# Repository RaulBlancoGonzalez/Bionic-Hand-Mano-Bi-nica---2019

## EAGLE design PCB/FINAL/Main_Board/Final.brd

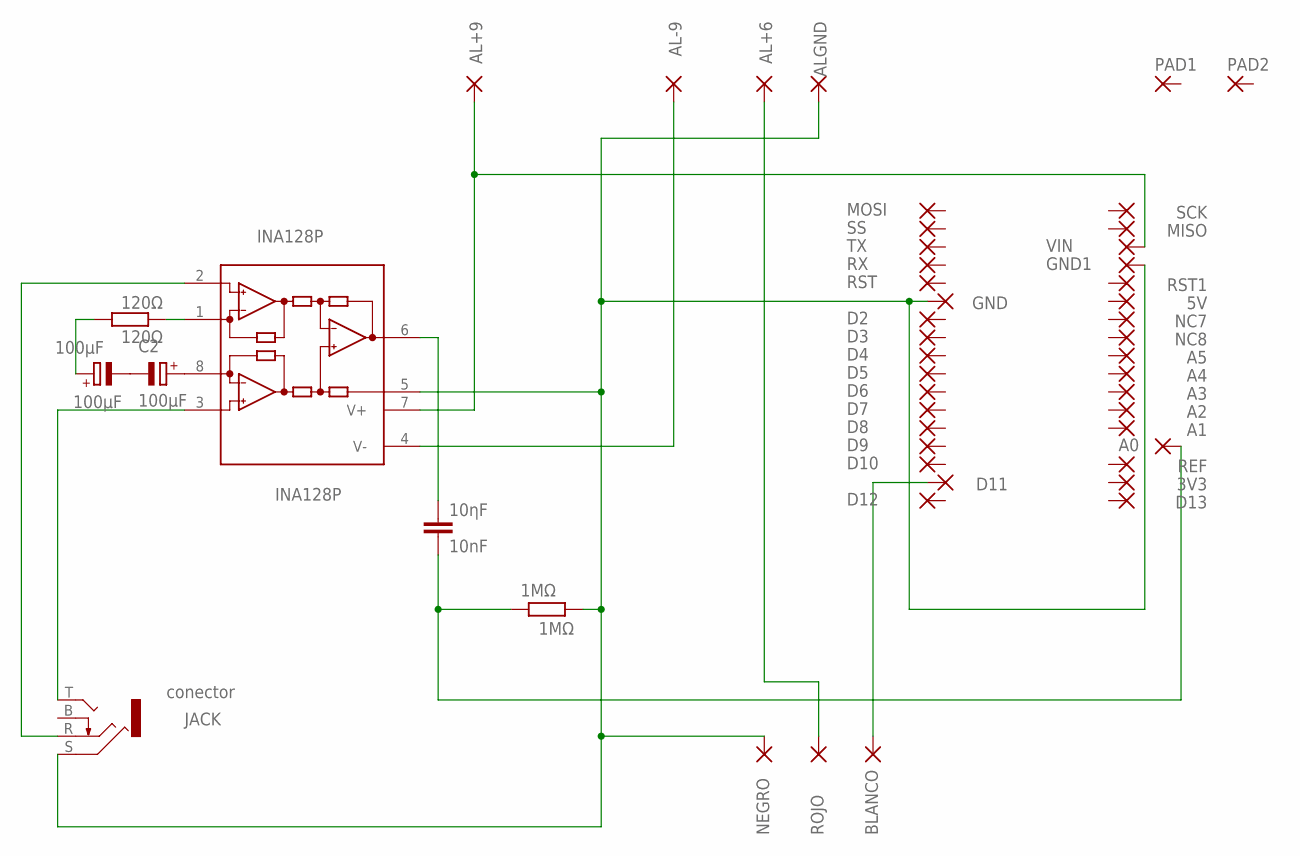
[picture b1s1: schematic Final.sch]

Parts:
1MΩ: 1MΩ; 0207/15
3V3, 5V: 1,6/0,9
10ηF: 10nF; C050-030X075
100μF: 100μF; B45181B
120Ω: 120Ω; 0207/15
A0, A1, A2, A3, A4, A5: 1,6/0,9
AL+6, AL+9: 1,6/0,9
AL-9: 1,6/0,9
ALGND: 1,6/0,9
BLANCO: 1,6/0,9
C2: 100μF; B45181B
D2, D3, D4, D5, D6, D7, D8, D9, D10, D11, D12, D13: 1,6/0,9
GND, GND1: 1,6/0,9
INA128P: INA128P; DIL08
JACK: conector; KLBR4
MISO: 1,6/0,9
MOSI: 1,6/0,9
NC7, NC8: 1,6/0,9
NEGRO: 1,6/0,9
PAD1, PAD2: 3,81/1,4
REF: 1,6/0,9
ROJO: 1,6/0,9
RST, RST1: 1,6/0,9
RX: 1,6/0,9
SCK: 1,6/0,9
SS: 1,6/0,9
TX: 1,6/0,9
VIN: 1,6/0,9

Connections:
+6VCC: AL+6.1, ROJO.1
+9VCC: AL+9.1, INA128P.7 (V+), VIN.1
-9VCC: AL-9.1, INA128P.4 (V-)
A0: 1MΩ.2, 10ηF.2, A0.1
CONTROL_SERVO: BLANCO.1, D11.1
E1: INA128P.2 (-IN), JACK.R
E2: INA128P.3 (+IN), JACK.T
GND: 1MΩ.1, ALGND.1, GND.1, GND1.1, INA128P.5 (REF), JACK.S, NEGRO.1
unnamed: C2.+, INA128P.8 (RG)
unnamed: 100μF.-, C2.-
unnamed: 120Ω.2, INA128P.1 (RG)
unnamed: 100μF.+, 120Ω.1
unnamed: 10ηF.1, INA128P.6 (OUT)

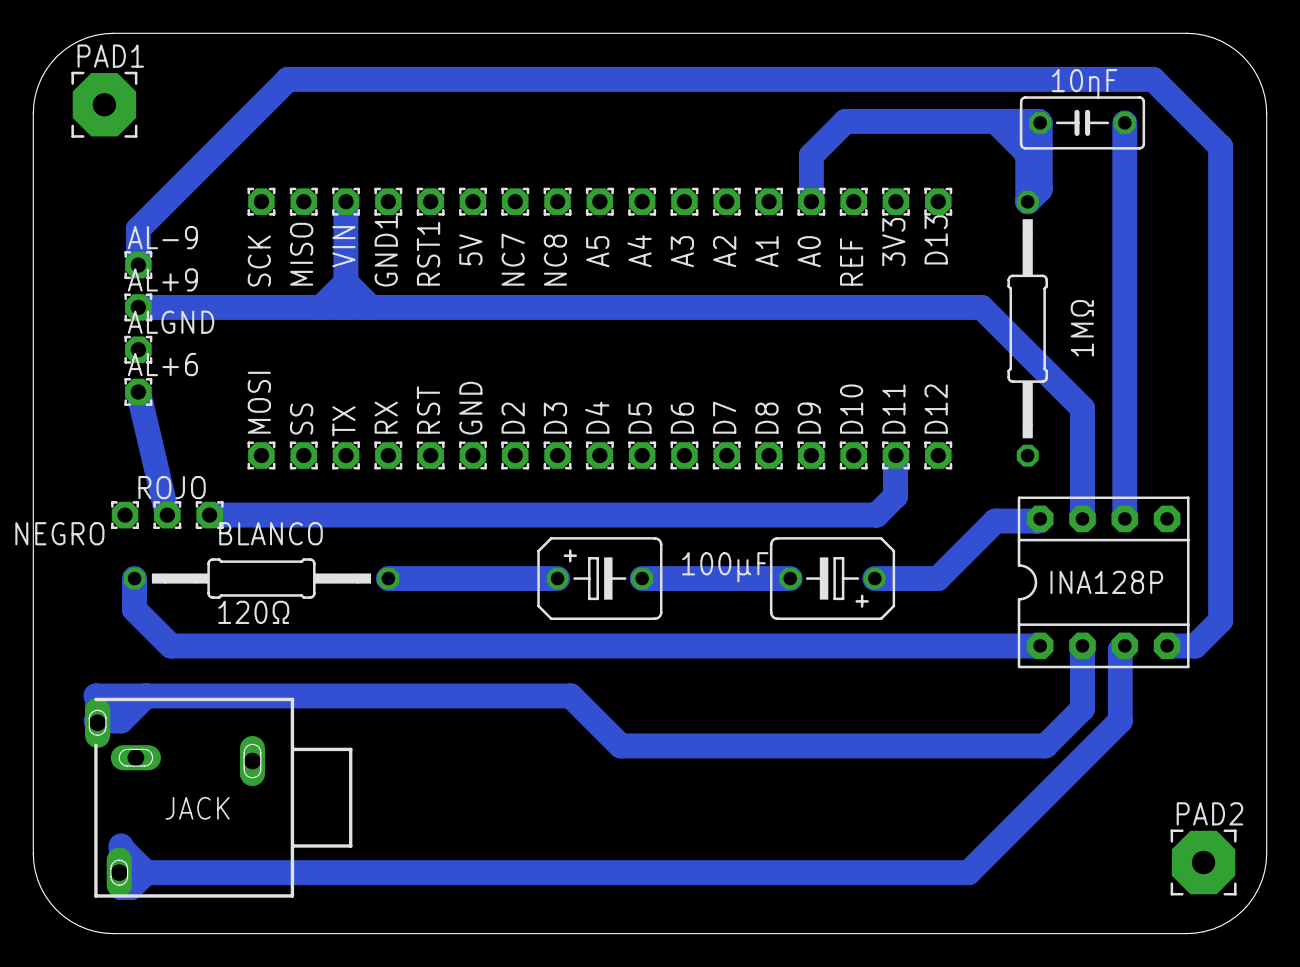
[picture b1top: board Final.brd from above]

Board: 2 copper layers, 74.1 x 54.1 mm, 50 parts (0 on the bottom side), 13 nets.

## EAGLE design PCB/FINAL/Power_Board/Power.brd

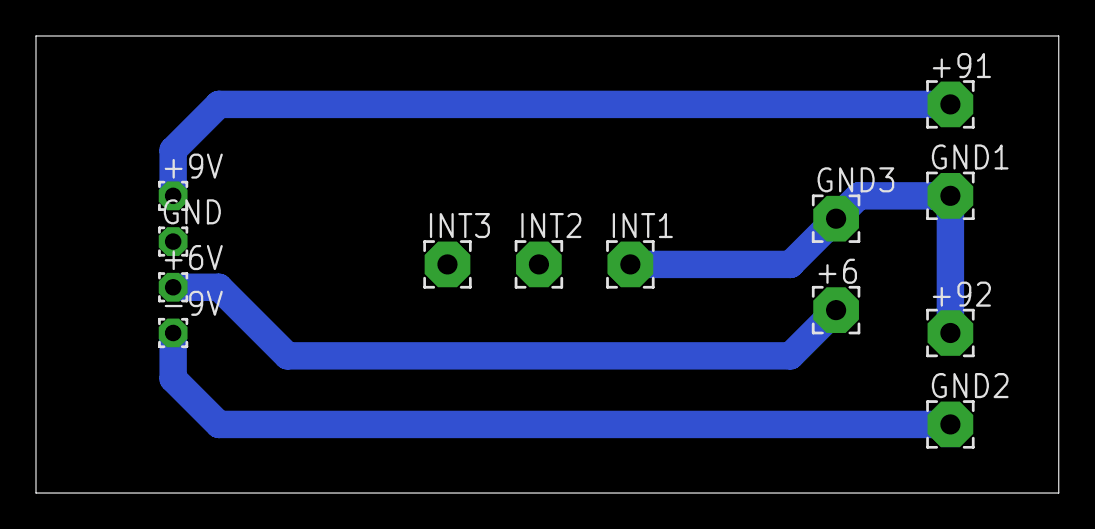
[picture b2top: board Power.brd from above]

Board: 2 copper layers, 56.8 x 25.4 mm, 13 parts (0 on the bottom side), 5 nets.

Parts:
+6, +91, +92: 2,54/1,1
+6V, +9V: 1,6/0,9
-9V: 1,6/0,9
GND: 1,6/0,9
GND1, GND2, GND3: 2,54/1,1
INT1, INT2, INT3: 2,54/1,1

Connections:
6POS: +6.1, +6V.1
9NEG: -9V.1, GND2.1
9POS: +9V.1, +91.1
GND: GND.1, INT2.1, INT3.1
NEG123: +92.1, GND1.1, GND3.1, INT1.1

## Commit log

2019-06-21 Subida del repo
2019-11-19 'Subida'
2019-11-19 'Subida_archivos_GERBER'
2019-11-19 'Borrado'
2019-11-19 'Actualizacion_+GERBERfiles'
